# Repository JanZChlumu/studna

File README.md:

# Projekt Studna
> Se skládá ze 2 nezávislých částí
> - Ochrana domácí vodárny
> - Měření výšky hladiny

## Ochrana domácí vodárny
Do studny je umístěn [hladinový spínač](./img/Instalace_2.png), který sepne při kriticky nízké hladině. Tím se odpojí (3 fázová) domácí vodárna, aby se systém nezavzdušnil a čerpadlo neshořelo. [Schema v rozvaděči](./HW/Silnoproud_ochrana_cerpadla/darling_ochrana.pdf)

## Měření výšky hladiny
Motivace:
- Do studny byl při rekonstrukci zaveden UTP kabel. 
- Pramen není příliš silný v letních měsících je třeba šetřit vodou.

Snaha byla o levné řešení, hlavně na straně senzoru, které v případě nefunkčnosti bude možné snadno upgradovat na "profi drahé" řešení.
Levné řešení (cena 10USD) je ultrazvukový modul více níže.
Drahé řešení je např. [hydrostatický snímač TSH-37](https://www.fiedler.company/sites/default/files/dokumenty/datasheet_tsh37.pdf) jeho cena (v roce 2025) je cca 8.000Kč.

Pro obě řešení zůstane stejná komunikace mezi senzorem a řídící jednotkou a to přes RS485. TSH-37 vyžaduje protokol Modbus RTU na což není SW momentálně připraven.

### Základní blokové schema:

- [Schema řídící jednotky](./HW/kicad/lcd/lcd.pdf)
- Schema Remote Sensor Unit neexistuje -  je poměrně triviální.

### Ultrazvukové čidlo
Waterproof Ultrasonic Module JSN-SR04T
[zajímavostí o modulu (schema a módy)](https://forum.mysensors.org/topic/11417/jsn-sr04t-distance-sensor-reliability-issue-fix/6)

**Limity a omezení**, __které možná ovlivní vaše rozhodnutí o jeho nepoužití__.
- Měřený rozsah je přibližně od 25cm do 230cm.
- Přesnost je **kvantována v krocích 1,7cm**.

Tyto limity se nedají v softwaru řídící jednotky nijak kompenzovat, jsou dány konstrukcí modulu JSN-SR04T.

Možné příčiny limitů:
- **"Kvantování"**: zvuk se ve vzduchu šíří přibližně rychlostí 343 m/s. Když se podíváme, jak daleko zvuk urazí za 1 mikrosekundu:

$$
d = v \cdot t = 343 \text{m/s} \cdot 1 \mu s = 0{,}000 343 \text{m} = 0{,}0343 \text{cm}
$$

Jelikož vzdálenost se měří tam i zpět, a nás zajímá jen cesta tam, **čas se dělíme dvěma**,a to znamená, že rozlišení senzoru závisí na **časovém rozlišení** měření:

Např. pokud vnitřní časovač v modulu meří s přesností 100µs, pak bude kvantovací krok:

$$
0{,}0343 \text{cm} \cdot 100 \mu \cdot \frac{1}{2} \approx 1{,}7 \text{cm}
$$

Myslím, že modul JSN-SR04T vyhodnocuje či vzorkuje echo s frekvencí cca 10kHz, tedy žádná sláva a **odtud plyne nepřesnost**.

- Ve vzdálenosti < než 25cm se nestačí odražené echo detekovat.
- Ve vzdálenosti > než cca 230cm či vyšší vnitřní čítač přeteče a modul vrátí maximální hodnotu. Pokud se žádné echo nevrátí (detektor míří do volného prostoru) maximální hodnota bývá v intervalu (230,250) cm. S jistou rezervou je měření validní **do 220 cm**.

#### Použitý mód JSN-SR04T
se měmí hodnotou rezistoru viz datasheet; Mode 3: Mode=120K (or short M2 bit directly) UART controlled output
The UART controlled output method outputs the measured distance value (hexadecimal number)
according to the UART communication format. In this method, the trigger command 0X55 signal
needs to be added to the RX pin. The module measures once every time the command is received. The foot outputs the measured
distance value. The command trigger cycle should be greater than 60ms

# SW
Snaha byla použít co nejjednodušší a kýmkoli lehce upravitelé řešení.

- Vývojové prostředí je Thonny
- Zdrojové kódy jsou v MicroPythonu.
	- Vše co je třeba do Raspberry Pico nahrát je ve složce ./SW/2Pico/ 
	- [Konfigurační soubor](./SW/2Pico/config.json) a provozní data jsou uložena v json souborech v file systému, protože Raspberry Pico nemá vlastní EEPROMku. Limit je max. 100tis přepsání, což je zcela dostatečné, protože json soubory se ukládaní jen sporadicky.
	- Použité knihovny (složka ./SW/2Pico/lib/ , jsou lehce upravené (projekty pod MIT licencemi), změny nejsou nikde zdokumentovány.
- Tvorba vlastních fontů pro LCD je popsána [zde](./SW/tools/fonts/README.md)

# TODOs & BUGs

- HW
	- PCB Control unit layout:
		- opravit všechna poudra tranzistorů; Momentálně se dá deska osadit, ale všechny tranzistory se musí debilně otočit o 120stupňů.
		- posunout kondenzátor C7; usnadní se montáž
	- [Navrhnout PCB pro Remote sensor Unit](./img/Instalace_1.png); aby to nevypadalo takto...
	- přidat STL model krabičky
- SW
	- Dopnit do Menu možnost konfigurovat průměr studny pro výpočet litrů.
	- Bug: shadow vs stored data - v podmenu Historie grafů se přepisuje nově změněná hodnota. Fix: v menu nespouštět měřící task.

# Finální produkt
Trochu fotodokumentace [více zde](./img/)

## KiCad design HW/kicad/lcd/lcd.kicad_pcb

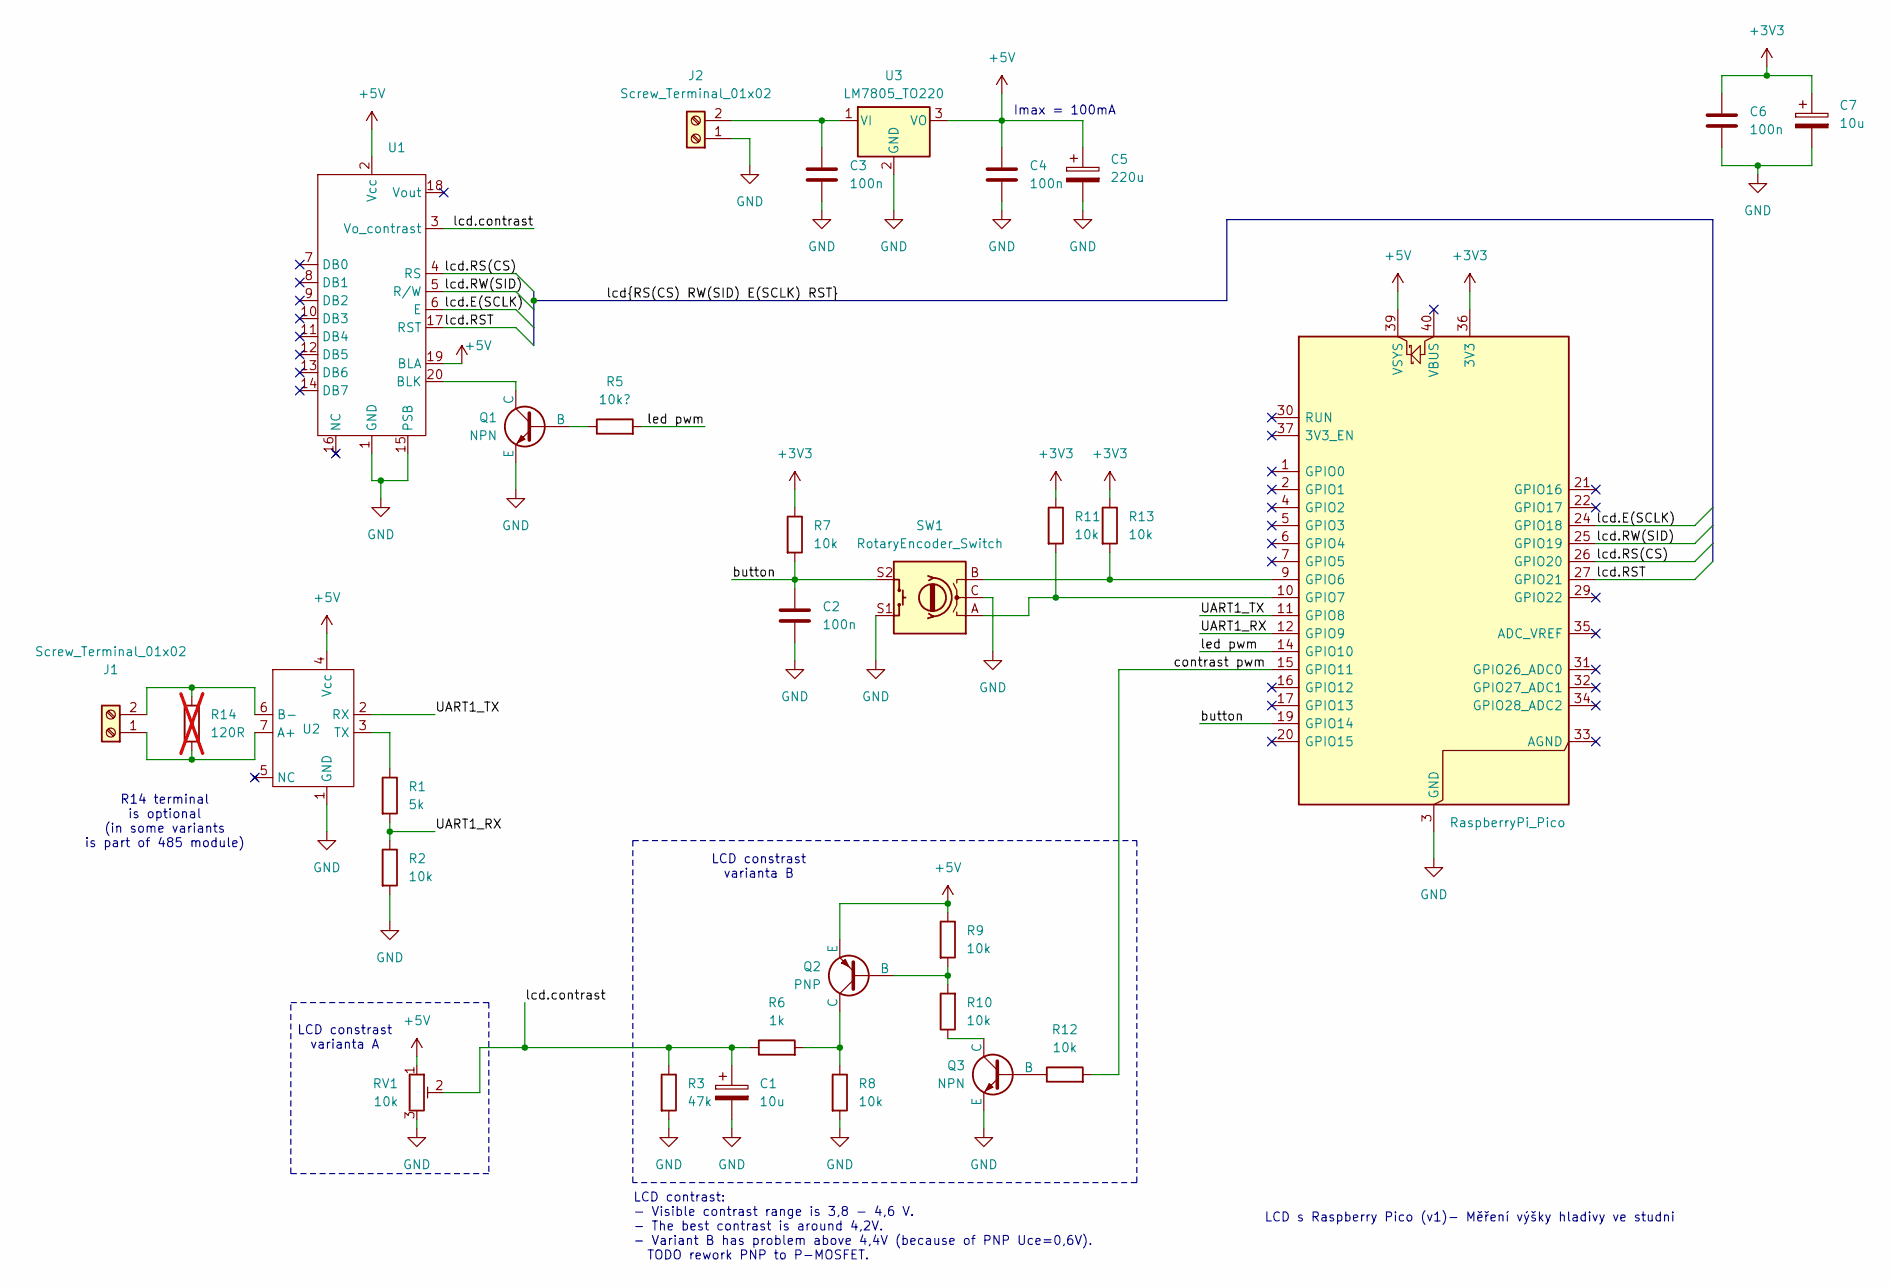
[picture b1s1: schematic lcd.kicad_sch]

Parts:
A1: RaspberryPi_Pico; RaspberryPi_Pico_Common_NO_wifi
C1, C7: 10u; CP_Radial_D5.0mm_P2.00mm
C2, C3, C4, C6: 100n; C_1206_3216Metric
C5: 220u; CP_Radial_D8.0mm_P2.50mm
J1, J2: Screw_Terminal_01x02; TerminalBlock_MaiXu_MX126-5.0-02P_1x02_P5.00mm
Q1, Q3: NPN; SOT-23
Q2: PNP; SOT-23
R1: 5k; R_1206_3216Metric
R2, R7, R8, R9, R10, R11, R12, R13: 10k; R_1206_3216Metric
R3: 47k; R_1206_3216Metric
R5: 10k?; R_1206_3216Metric
R6: 1k; R_1206_3216Metric
R14: 120R; R_1206_3216Metric; not fitted
RV1: 10k; Potentiometer_Runtron_RM-065_Vertical
SW1: RotaryEncoder_Switch; RotaryEncoder_Alps_EC11E-Switch_Vertical_H20mm
U1: LCD 128x64
U2: 485 modul
U3: LM7805_TO220; SOT-223-3_TabPin2

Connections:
+3V3: A1.36 (3V3), C6.1, C7.1, R7.1, R11.1, R13.1
+5V: A1.39 (VSYS), C4.1, C5.1, Q2.3 (E), R9.1, RV1.1, U1.2 (Vcc), U1.19 (BLA), U2.4 (Vcc), U3.3 (VO)
/UART1_RX: A1.12 (GPIO9), R1.2, R2.1
/UART1_TX: A1.11 (GPIO8), U2.2 (RX)
/button: A1.19 (GPIO14), C2.1, R7.2, SW1.S2
/contrast pwm: A1.15 (GPIO11), R12.2
/lcd.E(SCLK): A1.24 (GPIO18), U1.6 (E)
/lcd.RS(CS): A1.26 (GPIO20), U1.4 (RS)
/lcd.RST: A1.27 (GPIO21), U1.17 (RST)
/lcd.RW(SID): A1.25 (GPIO19), U1.5 (R/W)
/lcd.contrast: C1.1, R3.1, R6.1, RV1.2, U1.3 (Vo_contrast)
/led pwm: A1.14 (GPIO10), R5.2
GND: A1.3 (GND), A1.8 (GND), A1.13 (GND), A1.18 (GND), A1.23 (GND), A1.28 (GND), A1.38 (GND), C1.2, C2.2, C3.2, C4.2, C5.2, C6.2, C7.2, J2.1, Q1.3 (E), Q3.3 (E), R2.2, R3.2, R8.2, RV1.3, SW1.C, SW1.S1, U1.1 (GND), U1.15 (PSB), U2.1 (GND), U3.2 (GND); also elsewhere on the board
unnamed: A1.9 (GPIO6), R13.2, SW1.B
unnamed: A1.10 (GPIO7), R11.2, SW1.A
unnamed: J1.1, R14.2, U2.7 (A+)
unnamed: J1.2, R14.1, U2.6 (B-)
unnamed: C3.1, J2.2, U3.1 (VI)
unnamed: Q1.2 (B), R5.1
unnamed: Q1.1 (C), U1.20 (BLK)
unnamed: Q2.2 (B), R9.2, R10.2
unnamed: Q2.1 (C), R6.2, R8.1
unnamed: Q3.2 (B), R12.1
unnamed: Q3.1 (C), R10.1
unnamed: R1.1, U2.3 (TX)

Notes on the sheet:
LCD constrast varianta A
LCD s Raspberry Pico (v1)- Měření výšky hladivy ve studni
LCD constrast varianta B
LCD contrast: - Visible contrast range is 3,8 - 4,6 V. - The best contrast is around 4,2V. - Variant B has problem above 4,4V (because of PNP Uce=0,6V). TODO rework PNP to P-MOSFET.
R14 terminal is optional (in some variants is part of 485 module)
Imax = 100mA

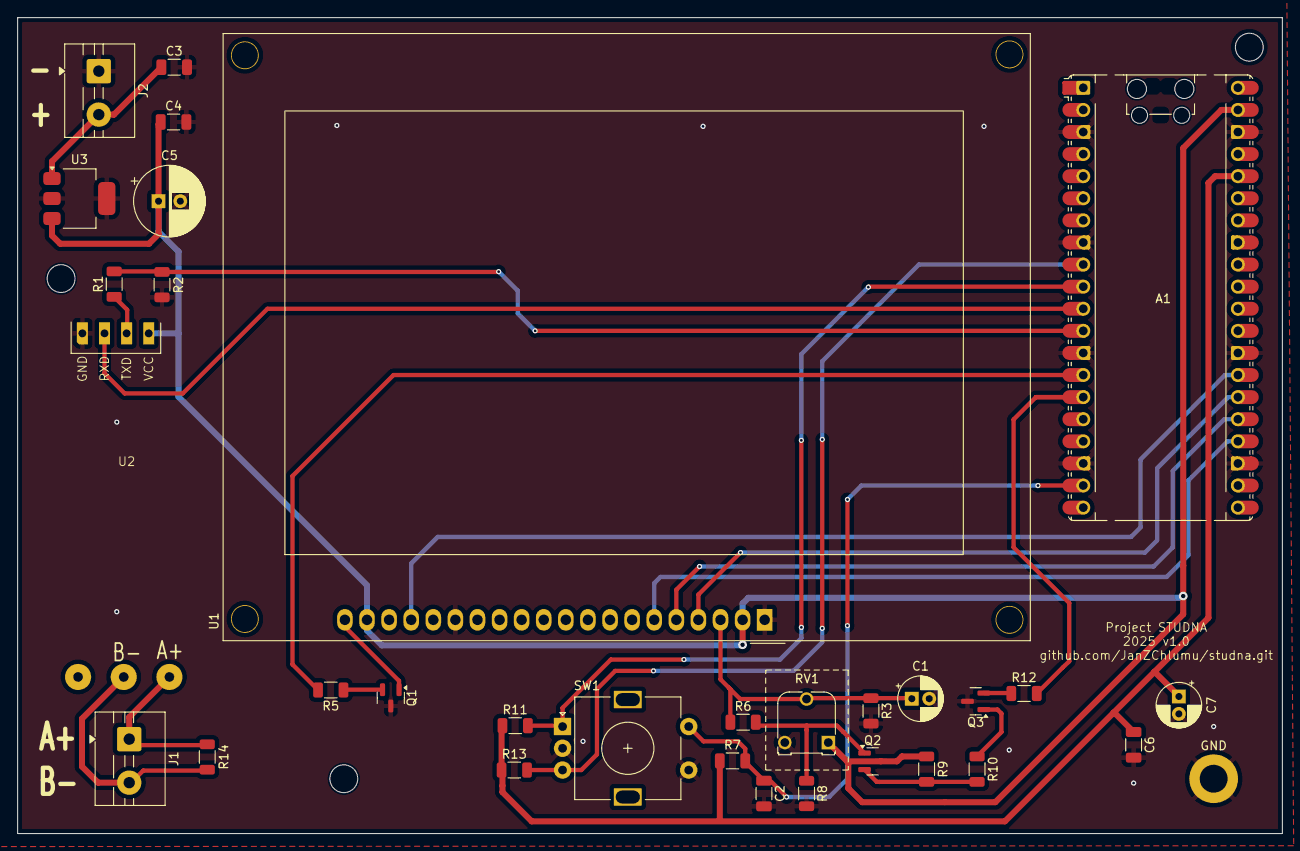
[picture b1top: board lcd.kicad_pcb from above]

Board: 2 copper layers, 145.4 x 93.8 mm, 32 parts (0 on the bottom side), 25 nets.

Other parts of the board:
GND: MountingHole_3.2mm_M3_DIN965_Pad

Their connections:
GND: GND.1; also elsewhere on the board

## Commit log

2025-03-26 pridano menu, ale nejsou nastaveny spravne promene
2025-03-27 uprava menu
2025-03-27 uprava logiky menu
2025-03-27 menu update
    rotary added getMaxVal
2025-03-27 timers changes to SW
2025-03-28 navrat z menu
2025-03-28 menu update
2025-03-28 navrat z menu, prvni akce
2025-03-28 otestovani CZ fontu
2025-03-29 opraveny font, uprava menu
2025-03-29 introduced konfigurace
2025-03-29 přejmenování menu
2025-03-29 neni SS
2025-03-30 ukladani barů a hodnot
2025-03-30 funkční menu, ukladani do pameti
2025-03-30 reset historická minima
2025-03-31 graph text over
2025-03-31 variable rename
2025-03-31 fonts
2025-03-31 center text - TODO test it!
2025-03-31 LCD font shift
2025-03-31 průměrování vzorků
2025-03-31 zarovnání a přejmenování textů
2025-03-31 graph text fix
2025-04-01 add Calibri12CZ
2025-04-01 semafor pro měření
2025-04-01 LCD clear -> fill ; lepší odezva
2025-04-01 přegenerovaný font s podporou spec. znaků
2025-04-01 new parameter clear_background
2025-04-03 uklid
2025-04-03 tools for lcd
2025-04-10 lcd pin change
2025-04-10 LCD rotation
2025-04-11 pwmKontrast
2025-04-13 update LCD pwm range
2025-04-14 Kicad LCD pcb
2025-04-15 change mounting holes
2025-04-18 pcb ramecek potenciometru
2025-04-18 schema ochraného obvodu vodárny
2025-04-24 re-order project structure
2025-05-12 small documentation update
2025-05-12 add pdf
2025-05-16 fix Copilot fuckup :/
2025-05-17 doc update, files path refactoring
2025-05-30 fix H-referece problems, change grahic info, update README
2025-06-23 1st production code
2025-06-29 production config data
2025-06-29 new home screen liters
2025-06-30 upodate documentation
2025-06-30 update documentation
2025-07-07 bug description
